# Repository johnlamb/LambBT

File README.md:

# LambBT
## Split wireless keyboard

A small 34 key split wireless keyboard with Choc V1 switches heavily inspired by the Sweep family and Architeuthis Dux. The columns have the same splay as the AD and is great for starting to experiment with splays.

The keyboard uses hotswap and a top plate together with a 3D printed case with M2 insets. 

Socketing the Nice!Nano v2 allows the battery to fit under the MCU. The MCU can face both up and down on either split. For a face up orientation, as in the pictures, solder the MCU bridges on the top. For a face down orientation, solder the MCU bridges on the bottom/back side.

I opted to skip an external battery JST connector and instead use two battery holes to solder the wires. Ensure right polarity, the positive end (usually red) goes in the left hole on the left split, and the right hole on the right split(towards the key switches) whereas the negative/ground (usually black) goes in the outer hole (right hole on the left split and left hole on the right split).

On/Off switch with a case cutout and a reset switch that wont be accidentally triggered.

## Design

Designed from the ground up using Ergogen and the routing in KiCad. Files for the pcb and case are in the [Ergogen](ergogen) folder together with ready made gerber files for both the pcb and plate.

Stl-files for the case are in the [output/case](ergogen/output/cases) folder.

## Build

To build for yourself, mae sure Ergogen CLI is installed. Then download/clone this repo, stand in the ergogen folder and issue the `ergogen .` command.

To also generate the case files, use the full:
`ergogen . && for i in output/cases/*.jscad; do npx @jscad/cli@1 "$i" -of stla ; done`

## Firmware
I use ZMK as firmware. You can find tested firmware and an initial keymap in the [lambbt_zmk repo](https://github.com/johnlamb/lambbt_zmk). Observer the standard keymap is Colemak-DH, if you want regular QWERTY, use the "default.keymap" file in the repo.

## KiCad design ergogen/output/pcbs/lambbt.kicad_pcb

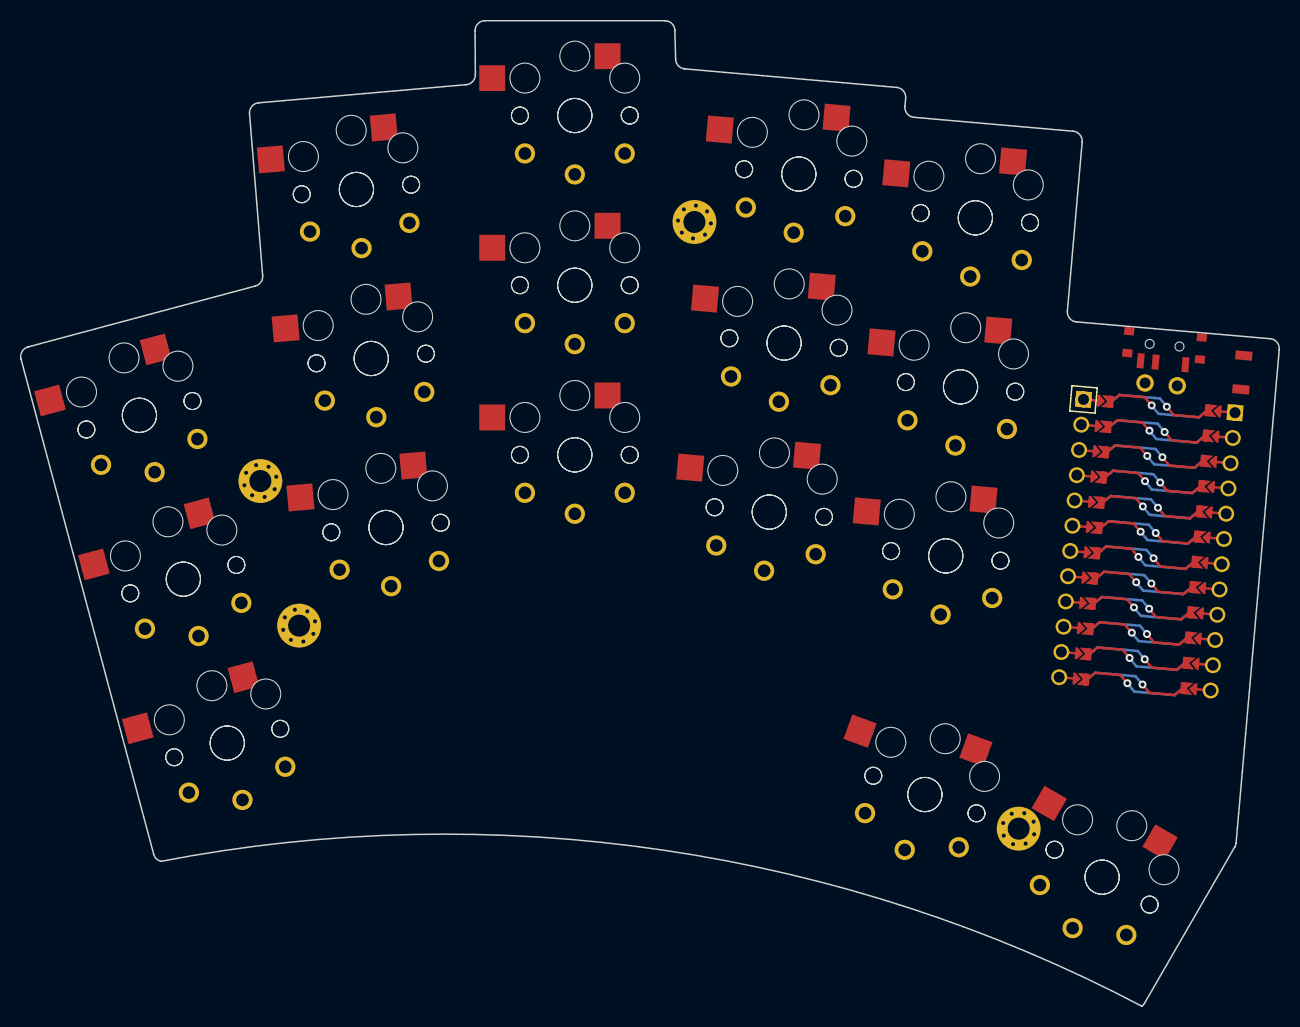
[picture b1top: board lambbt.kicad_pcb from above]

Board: 2 copper layers, 126.1 x 98.7 mm, 39 parts (0 on the bottom side), 18 nets.

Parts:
MCU1: ProMicro
S1, S2, S3, S4, S5, S6, S7, S8, S9, S10, S11, S12, S13, S14, S15, S16, S17, S18, S19, S20, S21, S22, S23, S24, S25, S26, S27, S28, S29, S30, S31, S32, S33, S34: PG1350
_4, _5, _6, _7: MountingHole_2.2mm_M2_Pad_Via

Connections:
GND: MCU1.2, MCU1.21, MCU1.22, S1.2, S2.2, S3.2, S4.2, S5.2, S6.2, S7.2, S8.2, S9.2, S10.2, S11.2, S12.2, S13.2, S14.2, S15.2, S16.2, S17.2, S18.2, S19.2, S20.2, S21.2, S22.2, S23.2, S24.2, S25.2, S26.2, S27.2, S28.2, S29.2, S30.2, S31.2, S32.2, S33.2, S34.2
P0: MCU1.23, S14.1, S31.1
P1: MCU1.24, S15.1, S32.1
P2: MCU1.20, S13.1, S30.1
P3: MCU1.19, S12.1, S29.1
P4: MCU1.18, S11.1, S28.1
P5: MCU1.17, S10.1, S27.1
P6: MCU1.16, S9.1, S26.1
P7: MCU1.15, S8.1, S25.1
P8: MCU1.14, S7.1, S24.1
P9: MCU1.13, S6.1, S23.1
P10: MCU1.12, S5.1, S22.1
P14: MCU1.10, S3.1, S20.1
P15: MCU1.9, S2.1, S19.1
P16: MCU1.11, S4.1, S21.1
P18: MCU1.8, S1.1, S18.1
P19: MCU1.7, S16.1, S33.1
P20: MCU1.6, S17.1, S34.1

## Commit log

2023-08-04 Initial
2023-08-09 Case shelf
2023-08-09 Documentation
2023-08-09 Clean up
2023-08-10 Clearlify battery connections
2023-08-10 Extra info
2023-12-10 Updated case and added magnetic case
